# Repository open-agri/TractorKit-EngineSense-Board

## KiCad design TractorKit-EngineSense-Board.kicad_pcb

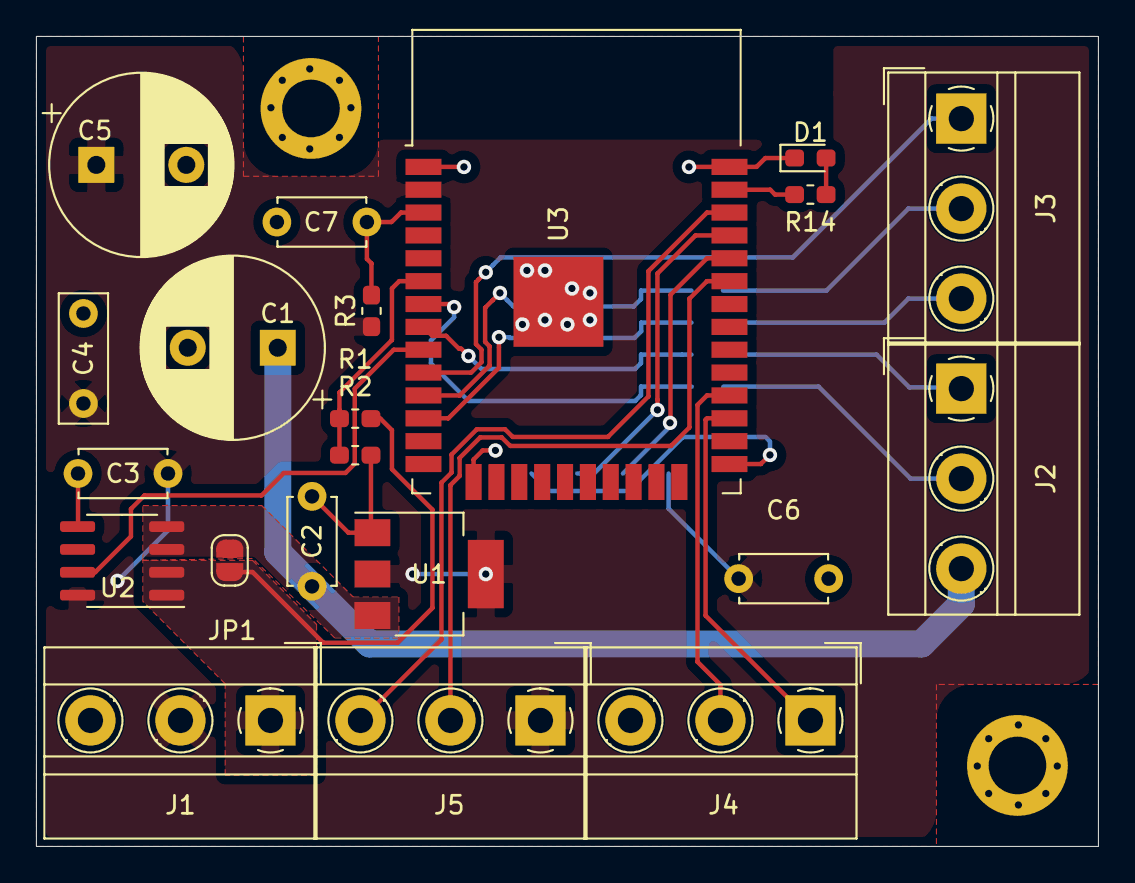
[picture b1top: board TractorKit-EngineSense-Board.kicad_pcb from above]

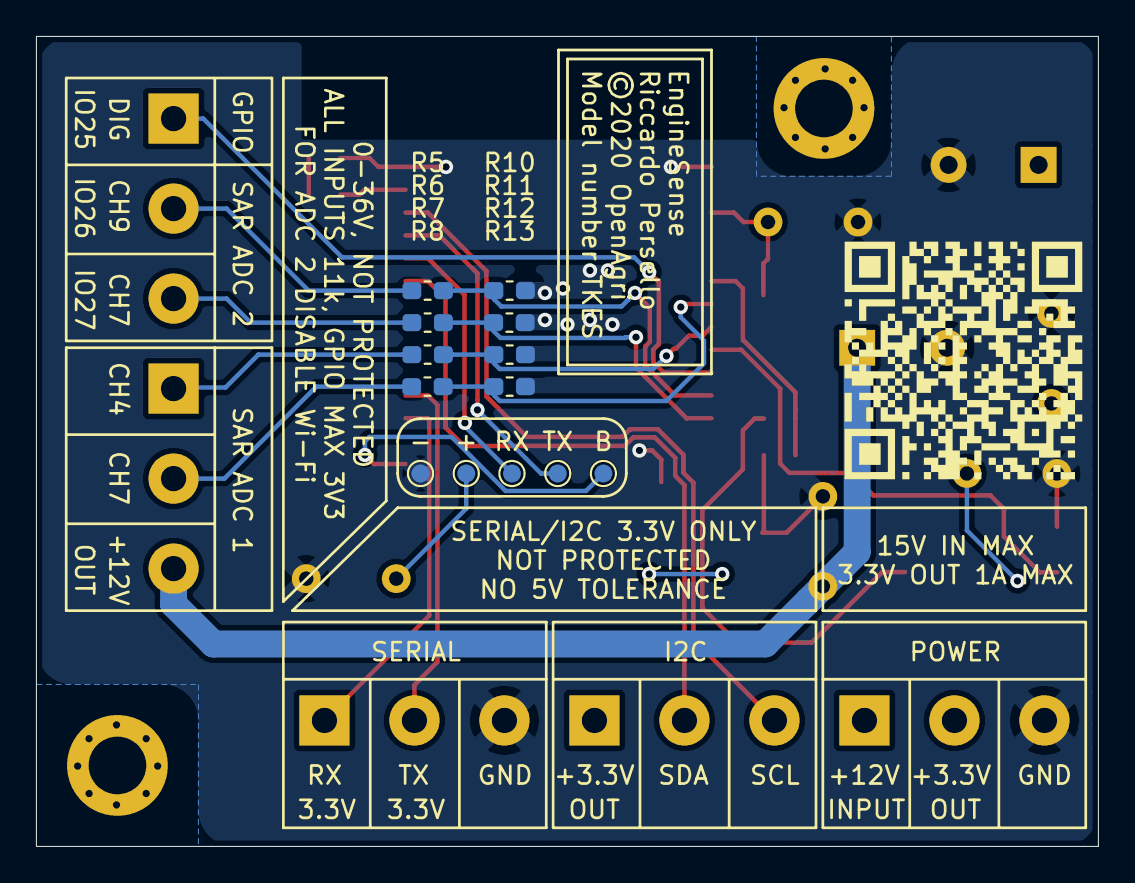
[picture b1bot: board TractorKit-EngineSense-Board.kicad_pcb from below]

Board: 2 copper layers, 59.0 x 45.0 mm, 37 parts (14 on the bottom side), 25 nets.

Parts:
 : MountingHole_3.2mm_M3_DIN965_Pad
 #2: MountingHole_3.2mm_M3_DIN965_Pad
 #3: open-agri.github.io_TKES1
+: SERVICE_3V3; TestPoint_Pad_D1.0mm
-: SERVICE_GND; TestPoint_Pad_D1.0mm
B: SERVICE_BOOT; TestPoint_Pad_D1.0mm
C1: 100u; CP_Radial_D10.0mm_P5.00mm
C2: 1u; C_Disc_D4.7mm_W2.5mm_P5.00mm
C3, C6, C7: 100n; C_Disc_D4.7mm_W2.5mm_P5.00mm
C4: 2.2u; C_Disc_D7.0mm_W2.5mm_P5.00mm
C5: 220u; CP_Radial_D10.0mm_P5.00mm
D1: LED; LED_0603_1608Metric_Pad1.05x0.95mm_HandSolder
J1: POWER; TerminalBlock_MetzConnect_Type011_RT05503HBWC_1x03_P5.00mm_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
J2: ADC1; TerminalBlock_MetzConnect_Type011_RT05503HBWC_1x03_P5.00mm_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
J3: ADC2; TerminalBlock_MetzConnect_Type011_RT05503HBWC_1x03_P5.00mm_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
J4: UART; TerminalBlock_MetzConnect_Type011_RT05503HBWC_1x03_P5.00mm_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
J5: I2C; TerminalBlock_MetzConnect_Type011_RT05503HBWC_1x03_P5.00mm_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
JP1: BYPASS; SolderJumper-2_P1.3mm_Open_RoundedPad1.0x1.5mm
R1, R3, R5, R6, R7, R8: 10k; R_0603_1608Metric_Pad1.05x0.95mm_HandSolder
R2, R10, R11, R12, R13: 1k; R_0603_1608Metric_Pad1.05x0.95mm_HandSolder
R14: R; R_0603_1608Metric_Pad1.05x0.95mm_HandSolder
RX: SERVICE_RX; TestPoint_Pad_D1.0mm
TX: SERVICE_TX; TestPoint_Pad_D1.0mm
U1: AMS1117-3.3; SOT-223-3_TabPin2
U2: ACS711xLCTR-12AB; SOIC-8_3.9x4.9mm_P1.27mm
U3: ESP32-WROOM-32

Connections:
+3V3: +.1, C3.1, C4.1, C5.1, C6.1, J1.2, J5.1, R3.1, U1.2, U2.8, U3.2
+12V: C1.1, C2.1, J2.3, JP1.1, U1.3, U2.3, U2.4
/12VIN: J1.1, JP1.2, R1.1, U2.1, U2.2
/ADC1_4: J2.1, R7.1
/ADC1_7: J2.2, R8.1
/ADC2_7: J3.3, R6.1
/ADC2_9: J3.2, R5.1
/AN_CURR: U2.7, U3.9
/AN_VOLT: R1.2, R2.1, U3.6
/DIGITAL: J3.1, U3.10
/PR_BOOT: B.1, U3.25
/PR_RX: RX.1, U3.34
/PR_TX: TX.1, U3.35
/RX: J4.1, U3.27
/SCL: J5.3, U3.36
/SDA: J5.2, U3.33
/TX: J4.2, U3.28
GND: -.1, C1.2, C2.2, C3.2, C4.2, C5.2, C6.2, C7.1, D1.1, J1.3, J4.3, R2.2, R10.2, R11.2, R12.2, R13.2, U1.1, U2.5, U3.1, U3.15, U3.38, U3.39
unnamed: C7.2, R3.2, U3.3
unnamed: D1.2, R14.2
unnamed: R5.2, R10.1, U3.11
unnamed: R6.2, R11.1, U3.12
unnamed: R7.2, R12.1, U3.8
unnamed: R8.2, R13.1, U3.7
unnamed: R14.1, U3.37

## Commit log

2020-07-23 Final schematic
2020-07-23 Final 2
2020-07-26 First complete draft.
2020-07-29 Moved to SMD components
2020-07-29 Holes with vias
2020-07-30 Ready for panelization

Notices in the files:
TractorKit-EngineSense-Board.kicad_pcb:
©2020 OpenAgri
